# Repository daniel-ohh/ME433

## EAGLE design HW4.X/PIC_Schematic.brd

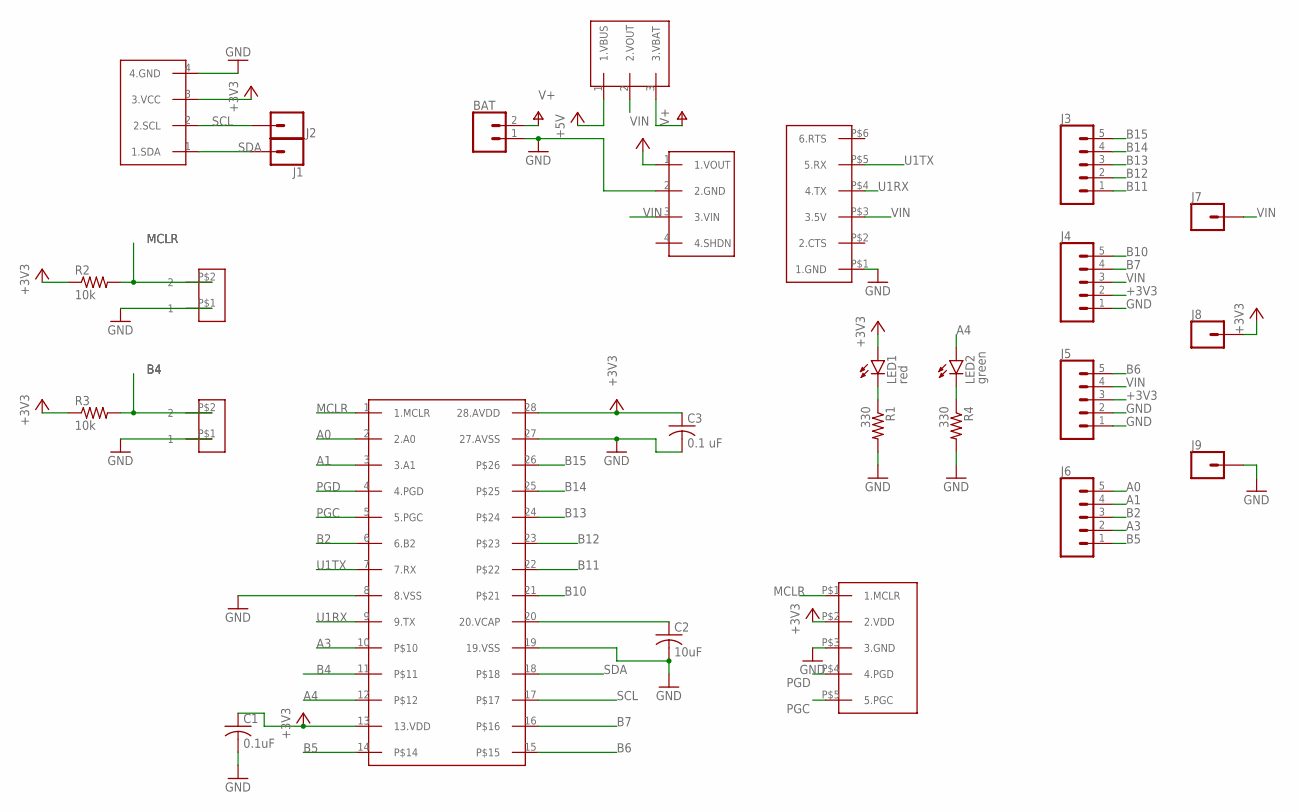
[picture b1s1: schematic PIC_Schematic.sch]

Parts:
BAT: CONN_02; 1X02
C1: 0.1uF; C025-024X044
C2: 10uF; C025-024X044
C3: 0.1 uF; C025-024X044
J1, J2, J7, J8, J9: CONN_01; 1X01
J3, J4, J5, J6: CONN_05; 1X05
LED1: red; LED3MM
LED2: green; LED3MM
R1, R4: 330; 0207/10
R2, R3: 10k; 0207/10
U$1: PIC32; DIL28-3
U$2: CP2104
U$3: SLIDE
U$4: VOLTREG
U$5: SNAP
U$6, U$7: PUSH
U$8: OLED

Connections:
+3V3: C1.1, C3.1, J4.2, J5.3, J8.1, LED1.A, R2.1, R3.1, U$1.13 (13.VDD), U$1.28 (28.AVDD), U$4.1 (1.VOUT), U$5.P$2 (2.VDD), U$8.3 (3.VCC)
+5V: U$3.1 (1.VBUS)
A0: J6.5, U$1.2 (2.A0)
A1: J6.4, U$1.3 (3.A1)
A3: J6.2, U$1.10
A4: LED2.A, U$1.12
B2: J6.3, U$1.6 (6.B2)
B4: R3.2, U$1.11, U$7.P$2 (2)
B5: J6.1, U$1.14
B6: J5.5, U$1.15
B7: J4.4, U$1.16
B10: J4.5, U$1.21
B11: J3.1, U$1.22
B12: J3.2, U$1.23
B13: J3.3, U$1.24
B14: J3.4, U$1.25
B15: J3.5, U$1.26
GND: BAT.1, C1.2, C2.2, C3.2, J4.1, J5.1, J5.2, J9.1, R1.2, R4.2, U$1.8 (8.VSS), U$1.19 (19.VSS), U$1.27 (27.AVSS), U$2.P$1 (1.GND), U$4.2 (2.GND), U$5.P$3 (3.GND), U$6.P$1 (1), U$7.P$1 (1), U$8.4 (4.GND)
MCLR: R2.2, U$1.1 (1.MCLR), U$5.P$1 (1.MCLR), U$6.P$2 (2)
unnamed: LED2.K (C), R4.1
unnamed: LED1.K (C), R1.1
unnamed: C2.1, U$1.20 (20.VCAP)
PGC: U$1.5 (5.PGC), U$5.P$5 (5.PGC)
PGD: U$1.4 (4.PGD), U$5.P$4 (4.PGD)
SCL: J2.1, U$1.17, U$8.2 (2.SCL)
SDA: J1.1, U$1.18, U$8.1 (1.SDA)
U1RX: U$1.9 (9.TX), U$2.P$4 (4.TX)
U1TX: U$1.7 (7.RX), U$2.P$5 (5.RX)
V+: BAT.2, U$3.3 (3.VBAT)
VIN: J4.3, J5.4, J7.1, U$2.P$3 (3.5V), U$3.2 (2.VOUT), U$4.3 (3.VIN)

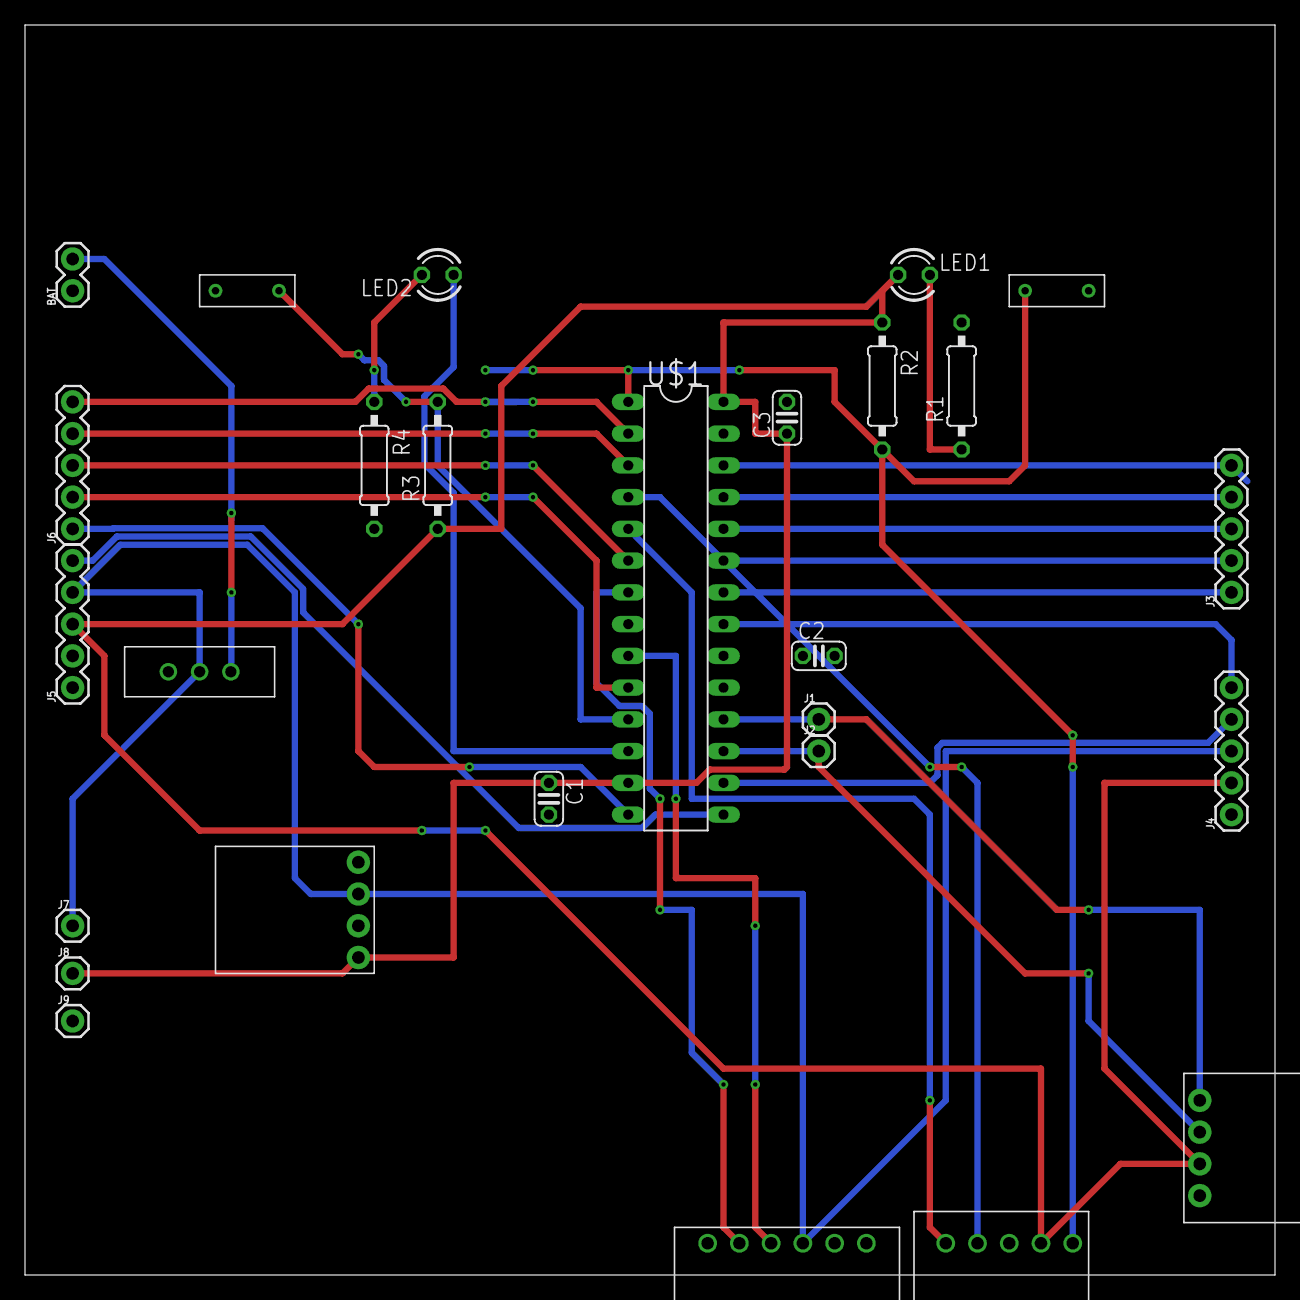
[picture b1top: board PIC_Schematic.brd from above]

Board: 2 copper layers, 100.0 x 100.0 mm, 27 parts (0 on the bottom side), 29 nets.

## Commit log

2022-04-07 hw3 edit
2022-04-22 hw 5
2022-05-12 hw10
2022-05-18 hw11

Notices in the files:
parts and their libraries:
SparkFun-Connectors: Licensing: Creative Commons ShareAlike 4.0 International - https://creativecommons.org/licenses/by-sa/4.0
